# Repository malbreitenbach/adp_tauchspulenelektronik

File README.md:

# adp_tauchspulenelektronik
ADP Tauchspulenelektronik (Versions-/Projektmanagement)

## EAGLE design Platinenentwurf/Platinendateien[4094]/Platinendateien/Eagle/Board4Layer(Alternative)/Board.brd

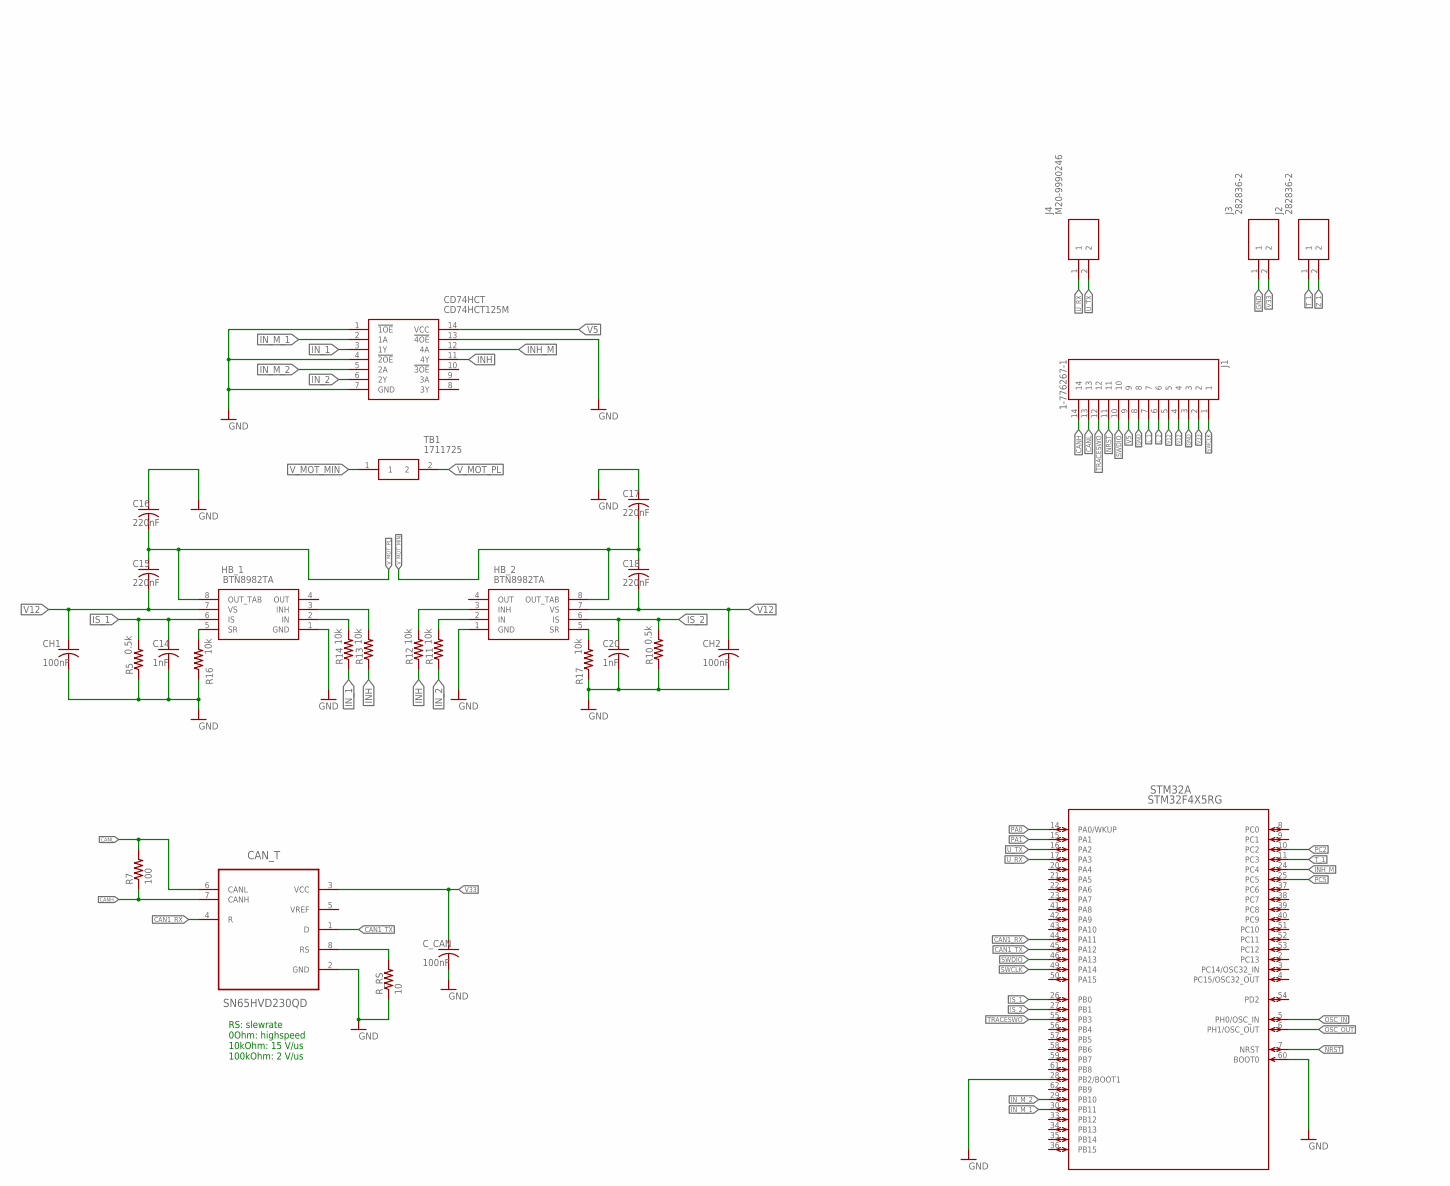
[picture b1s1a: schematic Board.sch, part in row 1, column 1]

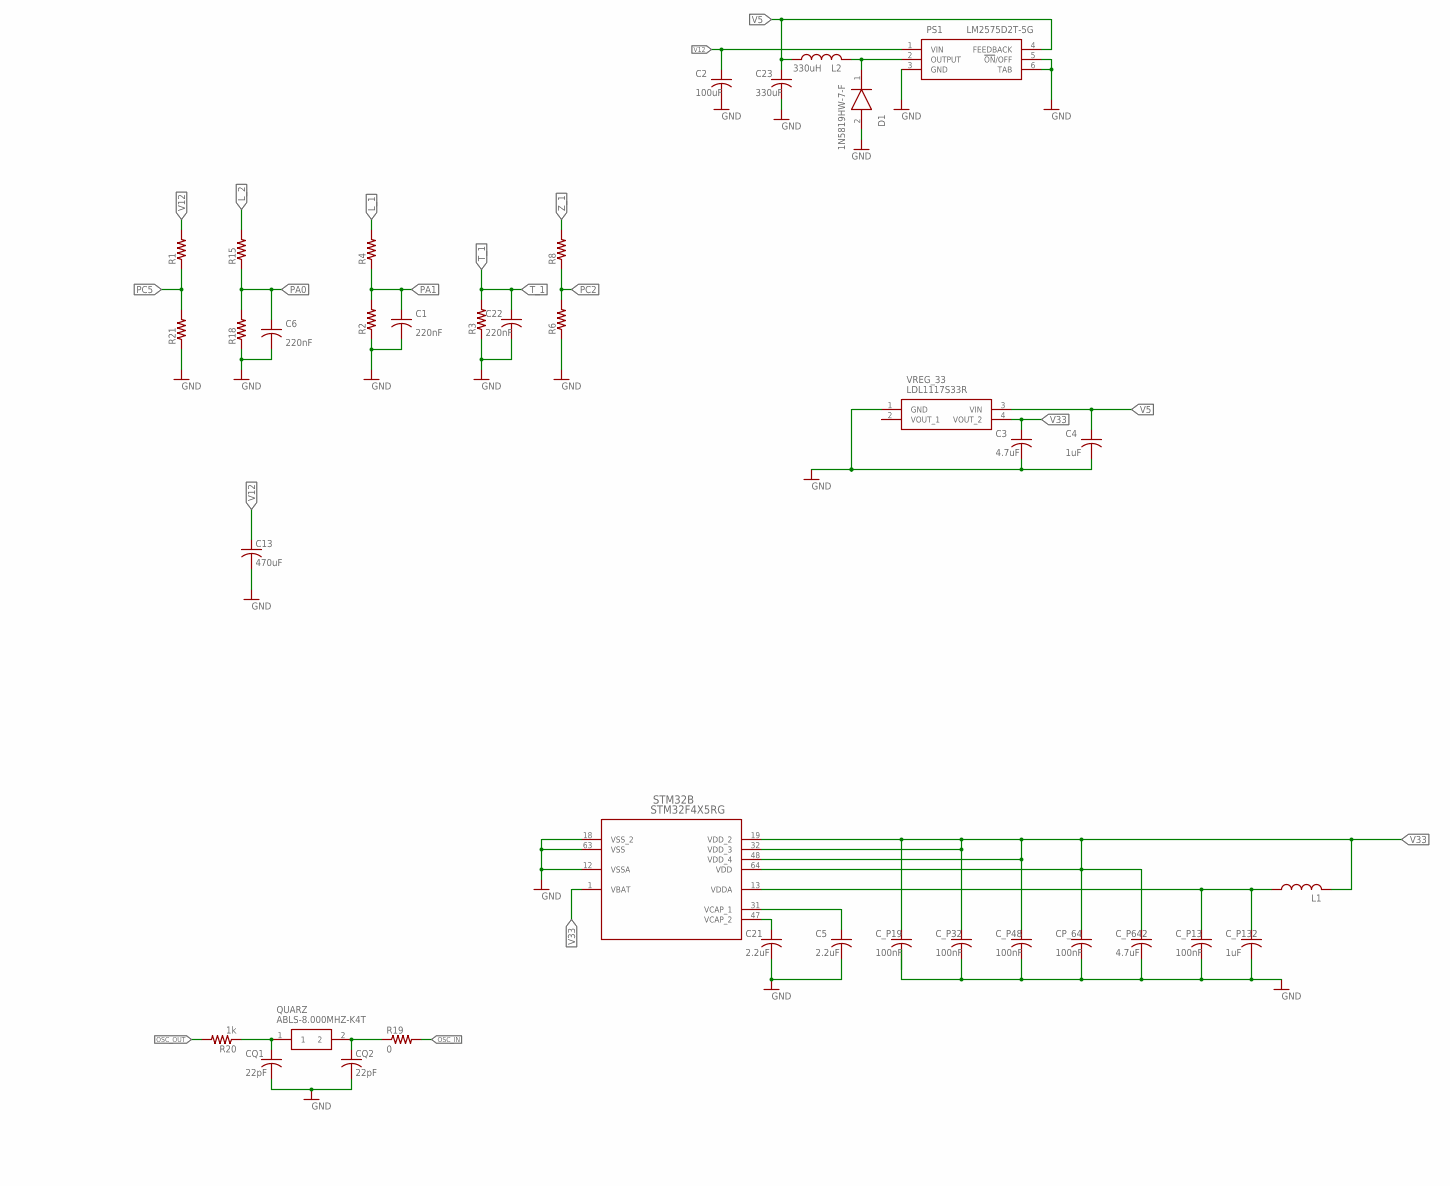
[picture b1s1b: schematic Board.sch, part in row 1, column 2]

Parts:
C1, C6, C15, C16, C17, C18, C22: 220nF; C0805
C2: 100uF; C0805
C3: 4.7uF; C0805
C4: 1uF; C0805
C5, C21: 2.2uF; C0805
C13: 470uF; C050-075X075
C14, C20: 1nF; C0805
C23: 330uF; C0805
CAN_T: SN65HVD230QD; SOIC127P600X175-8N; MPN SN65HVD230QD..
CD74HCT: CD74HCT125M; SOIC127P600X175-14N
CH1, CH2: 100nF; C0805
CP_64: 100nF; C0805
CQ1, CQ2: 22pF; C0805
C_CAN: 100nF; C0805
C_P13, C_P19, C_P32, C_P48: 100nF; C0805
C_P132: 1uF; C0805
C_P642: 4.7uF; C0805
D1: 1N5819HW-7-F; SOD3716X145N
HB_1, HB_2: BTN8982TA; TO127P1500X440-8N
J1: 1-776267-1; TE_1-776267-1
J2, J3: 282836-2; SHDR2W100P0X500_1X2_1000X820X1
J4: M20-9990246; HDRV2W64P0X254_1X2_508X254X864
L1: INDUCTOR_0805_N; RESC0805_N
L2: 330uH; RESC0805_N
PS1: LM2575D2T-5G; D2TSUFFIX-CASE936A-02-ISSUEC
QUARZ: ABLS-8.000MHZ-K4T; ABLS-12.000MHZ-B2; MPN ABLS-8.000MHZ-K4T
R1, R2, R3, R4, R6, R8, R15, R18, R21: R-US_R0805; R0805
R5, R10: 0.5k; R0805
R7: 100; R0805
R11, R12, R13, R14, R16, R17: 10k; R0805
R19: 0; R0805
R20: 1k; R0805
R_RS: 10; R0805
STM32: STM32F4X5RG; LQFP64-10X10MM
TB1: 1711725; PHEONIX-5.08PITCH-2PIN
VREG_33: LDL1117S33R; SOT230P700X180-4N; MPN LDL1117S33R

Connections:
CAN1_RX: CAN_T.4 (R), STM32.44 (PA11)
CAN1_TX: CAN_T.1 (D), STM32.45 (PA12)
CANH: CAN_T.7 (CANH), J1.14, R7.1
CANL: CAN_T.6 (CANL), J1.13, R7.2
CAN_RS: CAN_T.8 (RS), R_RS.2
GND: C1.2, C2.2, C3.2, C4.2, C5.2, C6.2, C13.2, C14.2, C16.1, C17.1, C20.2, C21.2, C22.2, C23.2, CAN_T.2 (GND), CD74HCT.1 (!1OE), CD74HCT.4 (!2OE), CD74HCT.7 (GND), CD74HCT.13 (!4OE), CH1.2, CH2.2, CP_64.2, CQ1.2, CQ2.2, C_CAN.2, C_P13.2, C_P19.2, C_P32.2, C_P48.2, C_P132.2, C_P642.2, D1.2 (A), HB_1.1 (GND), HB_2.1 (GND), J1.3, J1.8, J3.1, PS1.3 (GND), PS1.5 (!ON!/OFF), PS1.6 (TAB), R2.1, R3.1, R5.1, R6.1, R10.1, R16.1, R17.1, R18.1, R21.1, R_RS.1, STM32.12 (VSSA), STM32.18 (VSS_2), STM32.28 (PB2/BOOT1), STM32.60 (BOOT0), STM32.63 (VSS), VREG_33.1 (GND)
HB1_IN: HB_1.2 (IN), R14.2
HB1_INH: HB_1.3 (INH), R13.2
HB2_IN: HB_2.2 (IN), R11.2
HB2_INH: HB_2.3 (INH), R12.2
INH: CD74HCT.11 (4Y), R12.1, R13.1
INH_M: CD74HCT.12 (4A), STM32.24 (PC4)
IN_1: CD74HCT.3 (1Y), R14.1
IN_2: CD74HCT.6 (2Y), R11.1
IN_M_1: CD74HCT.2 (1A), STM32.30 (PB11)
IN_M_2: CD74HCT.5 (2A), STM32.29 (PB10)
IS_1: C14.1, HB_1.6 (IS), R5.2, STM32.26 (PB0)
IS_2: C20.1, HB_2.6 (IS), R10.2, STM32.27 (PB1)
L_1: J1.7, R4.2
L_2: J1.6, R15.2
unnamed: D1.1 (K), L2.2, PS1.2 (OUTPUT)
NRST: J1.11, STM32.7 (NRST)
OSC_IN: R19.2, STM32.5 (PH0/OSC_IN)
OSC_OUT: R20.2, STM32.6 (PH1/OSC_OUT)
PA0: C6.1, R15.1, R18.2, STM32.14 (PA0/WKUP)
PA1: C1.1, R2.2, R4.1, STM32.15 (PA1)
PC2: R6.2, R8.1, STM32.10 (PC2)
PC5: R1.1, R21.2, STM32.25 (PC5)
Q_IN: CQ2.1, QUARZ.2, R19.1
Q_OUT: CQ1.1, QUARZ.1, R20.1
SR1: HB_1.5 (SR), R16.2
SR2: HB_2.5 (SR), R17.2
SWCLK: J1.1, STM32.49 (PA14)
SWDIO: J1.10, STM32.46 (PA13)
TRACESWO: J1.12, STM32.55 (PB3)
T_1: C22.1, J2.1, R3.2, STM32.11 (PC3)
U_RX: J4.1, STM32.17 (PA3)
U_TX: J4.2, STM32.16 (PA2)
V5: C4.1, C23.1, CD74HCT.14 (VCC), J1.9, L2.1, PS1.4 (FEEDBACK), VREG_33.3 (VIN)
V12: C2.1, C13.1, C15.2, C18.2, CH1.1, CH2.1, HB_1.7 (VS), HB_2.7 (VS), J1.4, J1.5, PS1.1 (VIN), R1.2
V33: C3.1, CAN_T.3 (VCC), CP_64.1, C_CAN.1, C_P19.1, C_P32.1, C_P48.1, C_P642.1, J1.2, J3.2, L1.2, STM32.1 (VBAT), STM32.19 (VDD_2), STM32.32 (VDD_3), STM32.48 (VDD_4), STM32.64 (VDD), VREG_33.4 (VOUT_2)
VCAP_1: C5.1, STM32.31 (VCAP_1)
VCAP_2: C21.1, STM32.47 (VCAP_2)
VDDA: C_P13.1, C_P132.1, L1.1, STM32.13 (VDDA)
V_MOT_MIN: C17.2, C18.1, HB_2.8 (OUT_TAB), TB1.1
V_MOT_PL: C15.1, C16.2, HB_1.8 (OUT_TAB), TB1.2
Z_1: J2.2, R8.2

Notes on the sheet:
RS: slewrate 0Ohm: highspeed 10kOhm: 15 V/us 100kOhm: 2 V/us

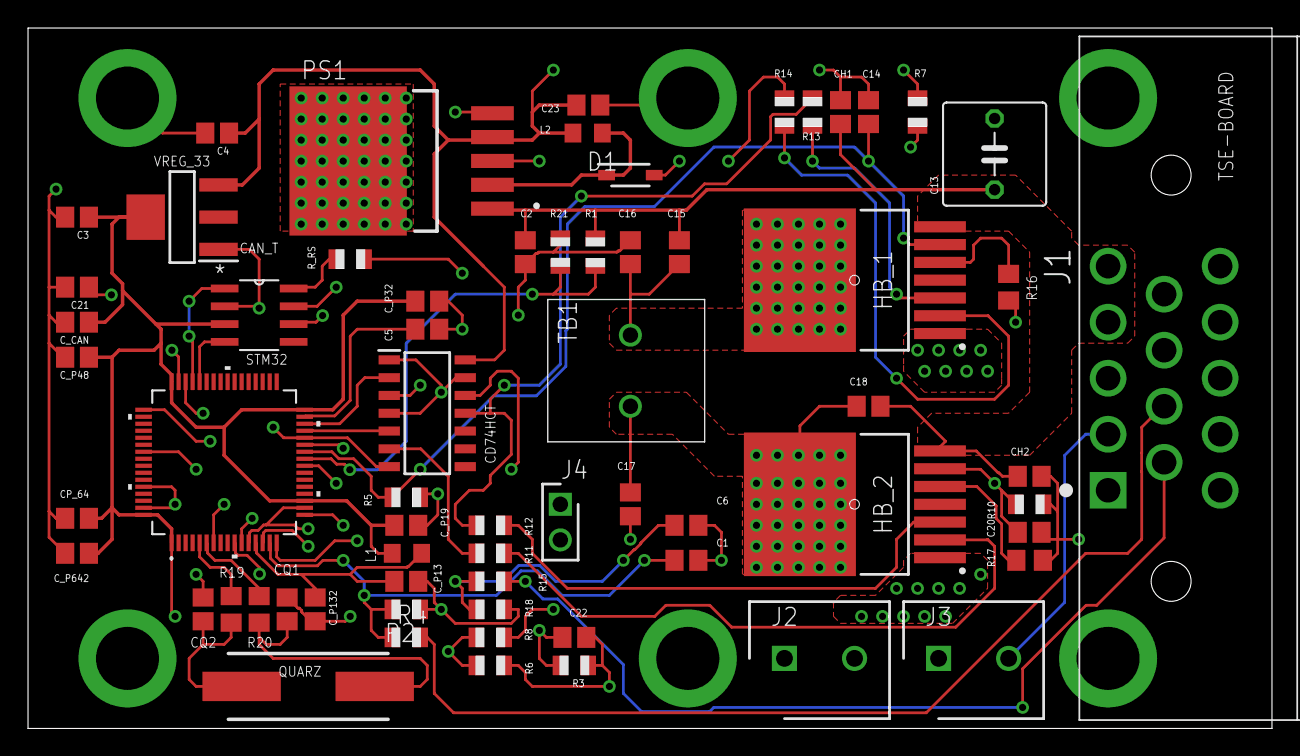
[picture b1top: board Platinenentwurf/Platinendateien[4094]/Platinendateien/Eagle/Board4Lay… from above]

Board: 4 copper layers, 88.8 x 50.0 mm, 65 parts (0 on the bottom side), 47 nets.

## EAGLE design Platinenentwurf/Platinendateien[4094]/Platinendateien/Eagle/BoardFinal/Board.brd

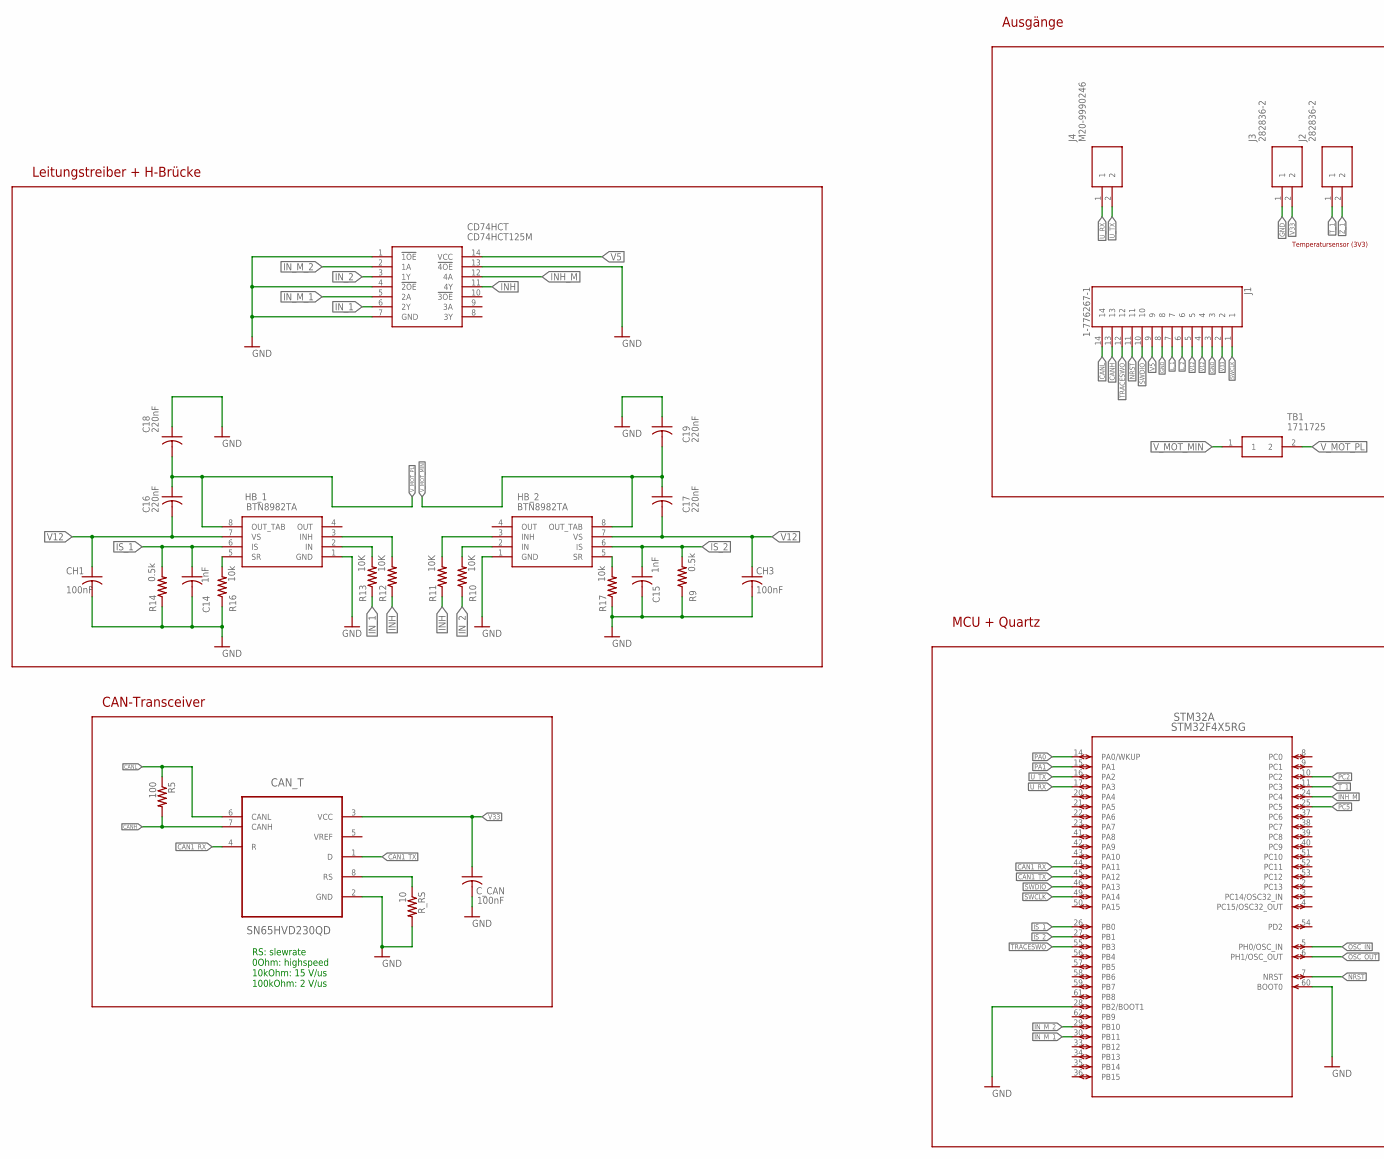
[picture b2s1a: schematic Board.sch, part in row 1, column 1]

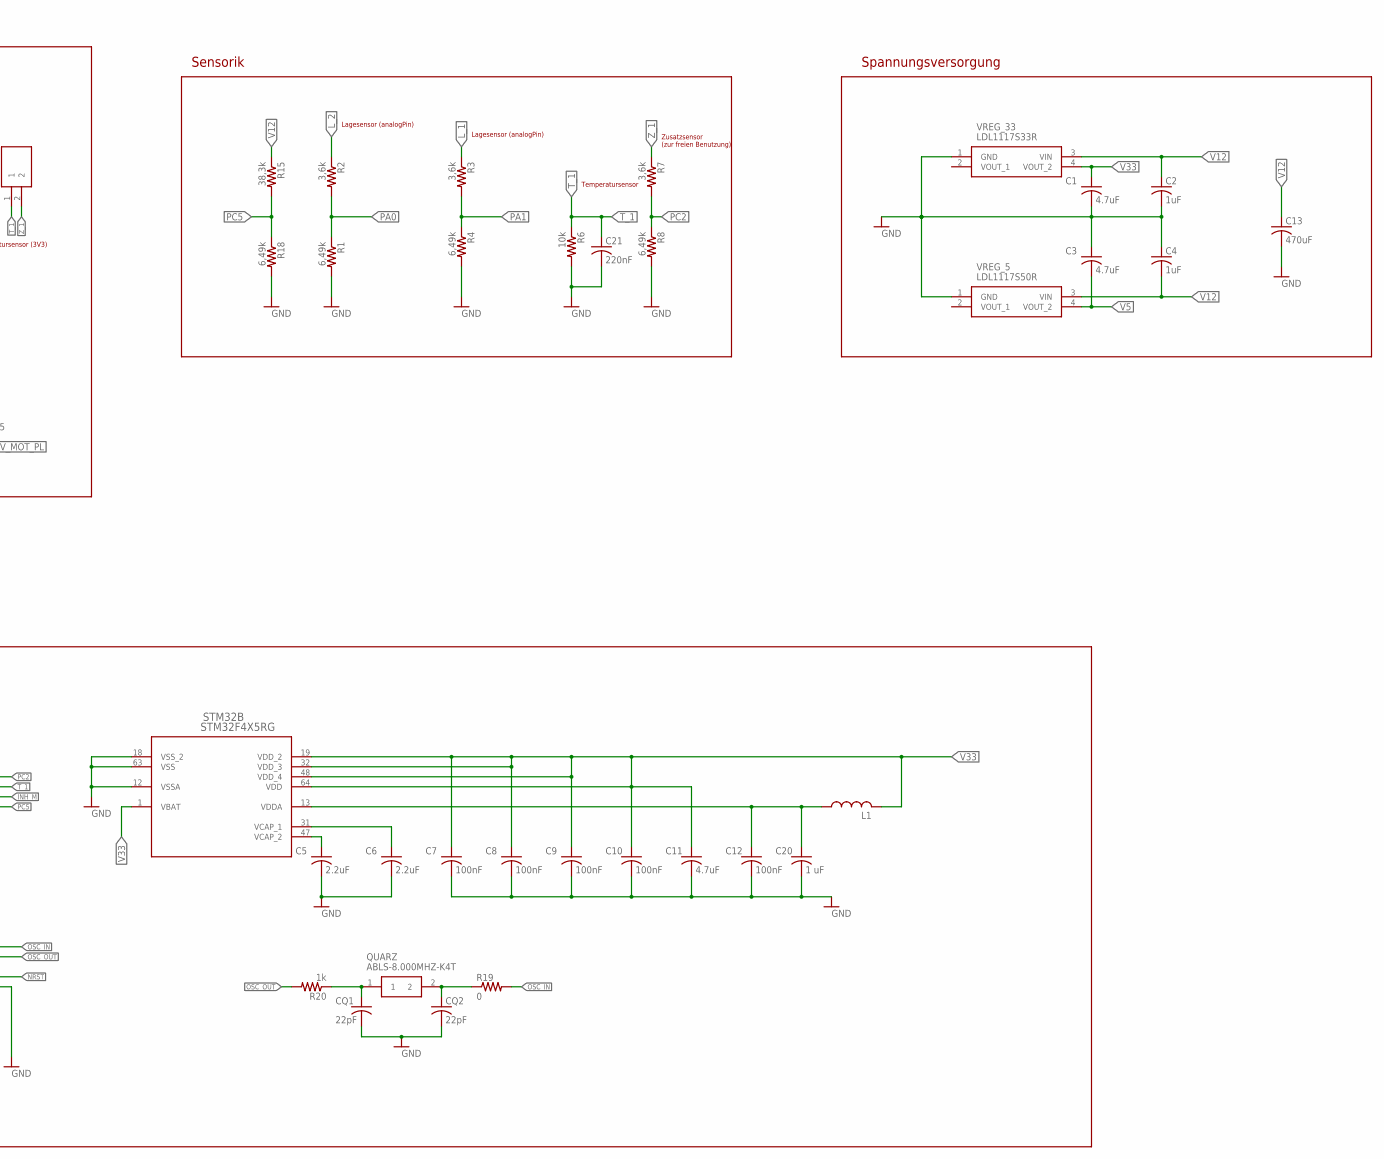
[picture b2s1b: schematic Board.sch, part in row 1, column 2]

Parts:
C1, C3, C11: 4.7uF; C1206
C2, C4: 1uF; C1206
C5, C6: 2.2uF; C1206
C7, C8, C9, C10, C12: 100nF; C1206
C13: 470uF; C050-075X075
C14, C15: 1nF; C1206
C16, C17, C18, C19, C21: 220nF; C1206
C20: 1 uF; C1206
CAN_T: SN65HVD230QD; SOIC127P600X175-8N; MPN SN65HVD230QD..
CD74HCT: CD74HCT125M; SOIC127P600X175-14N
CH1, CH3: 100nF; C1206
CQ1, CQ2: 22pF; C0805
C_CAN: 100nF; C1206
HB_1, HB_2: BTN8982TA; TO127P1500X440-8N
J1: 1-776267-1; TE_1-776267-1
J2, J3: 282836-2; SHDR2W100P0X500_1X2_1000X820X1
J4: M20-9990246; HDRV2W64P0X254_1X2_508X254X864
L1: INDUCTOR_0805_N; RESC0805_N
QUARZ: ABLS-8.000MHZ-K4T; ABLS-12.000MHZ-B2; MPN ABLS-8.000MHZ-K4T
R1, R4, R8, R18: 6,49k; R1206
R2, R3, R7: 3,6k; R1206
R5: 100; R1206
R6: 10k; R1206
R9, R14: 0.5k; R1206
R10, R11, R12, R13: 10K; R1206
R15: 38,3k; R1206
R16, R17: 10k; R0805
R19: 0; R0805
R20: 1k; R0805
R_RS: 10; R1206
STM32: STM32F4X5RG; LQFP64-10X10MM
TB1: 1711725; PHEONIX-5.08PITCH-2PIN
VREG_5: LDL1117S50R; SOT230P700X180-4N; MPN LDL1117S50R
VREG_33: LDL1117S33R; SOT230P700X180-4N; MPN LDL1117S33R

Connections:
CAN1_RX: CAN_T.4 (R), STM32.44 (PA11)
CAN1_TX: CAN_T.1 (D), STM32.45 (PA12)
CANH: CAN_T.7 (CANH), J1.13, R5.2
CANL: CAN_T.6 (CANL), J1.14, R5.1
CAN_RS: CAN_T.8 (RS), R_RS.1
GND: C1.2, C2.2, C3.1, C4.1, C5.2, C6.2, C7.2, C8.2, C9.2, C10.2, C11.2, C12.2, C13.2, C14.2, C15.2, C18.1, C19.1, C20.2, C21.2, CAN_T.2 (GND), CD74HCT.1 (!1OE), CD74HCT.4 (!2OE), CD74HCT.7 (GND), CD74HCT.13 (!4OE), CH1.2, CH3.2, CQ1.2, CQ2.2, C_CAN.2, HB_1.1 (GND), HB_2.1 (GND), J1.3, J1.8, J3.1, R1.2, R4.2, R6.2, R8.2, R9.1, R14.1, R16.1, R17.1, R18.2, R_RS.2, STM32.12 (VSSA), STM32.18 (VSS_2), STM32.28 (PB2/BOOT1), STM32.60 (BOOT0), STM32.63 (VSS), VREG_5.1 (GND), VREG_33.1 (GND)
HB1_IN: HB_1.2 (IN), R13.2
HB1_INH: HB_1.3 (INH), R12.2
HB2_IN: HB_2.2 (IN), R10.2
HB2_INH: HB_2.3 (INH), R11.2
INH: CD74HCT.11 (4Y), R11.1, R12.1
INH_M: CD74HCT.12 (4A), STM32.24 (PC4)
IN_1: CD74HCT.6 (2Y), R13.1
IN_2: CD74HCT.3 (1Y), R10.1
IN_M_1: CD74HCT.5 (2A), STM32.30 (PB11)
IN_M_2: CD74HCT.2 (1A), STM32.29 (PB10)
IS_1: C14.1, HB_1.6 (IS), R14.2, STM32.26 (PB0)
IS_2: C15.1, HB_2.6 (IS), R9.2, STM32.27 (PB1)
L_1: J1.7, R3.1
L_2: J1.6, R2.1
NRST: J1.11, STM32.7 (NRST)
OSC_IN: R19.2, STM32.5 (PH0/OSC_IN)
OSC_OUT: R20.2, STM32.6 (PH1/OSC_OUT)
PA0: R1.1, R2.2, STM32.14 (PA0/WKUP)
PA1: R3.2, R4.1, STM32.15 (PA1)
PC2: R7.2, R8.1, STM32.10 (PC2)
PC5: R15.2, R18.1, STM32.25 (PC5)
Q_IN: CQ2.1, QUARZ.2, R19.1
Q_OUT: CQ1.1, QUARZ.1, R20.1
SR1: HB_1.5 (SR), R16.2
SR2: HB_2.5 (SR), R17.2
SWCLK: J1.1, STM32.49 (PA14)
SWDIO: J1.10, STM32.46 (PA13)
TRACESWO: J1.12, STM32.55 (PB3)
T_1: C21.1, J2.1, R6.1, STM32.11 (PC3)
U_RX: J4.1, STM32.17 (PA3)
U_TX: J4.2, STM32.16 (PA2)
V5: C3.2, CD74HCT.14 (VCC), J1.9, VREG_5.4 (VOUT_2)
V12: C2.1, C4.2, C13.1, C16.2, C17.2, CH1.1, CH3.1, HB_1.7 (VS), HB_2.7 (VS), J1.4, J1.5, R15.1, VREG_5.3 (VIN), VREG_33.3 (VIN)
V33: C1.1, C7.1, C8.1, C9.1, C10.1, C11.1, CAN_T.3 (VCC), C_CAN.1, J1.2, J3.2, L1.2, STM32.1 (VBAT), STM32.19 (VDD_2), STM32.32 (VDD_3), STM32.48 (VDD_4), STM32.64 (VDD), VREG_33.4 (VOUT_2)
VCAP_1: C6.1, STM32.31 (VCAP_1)
VCAP_2: C5.1, STM32.47 (VCAP_2)
VDDA: C12.1, C20.1, L1.1, STM32.13 (VDDA)
V_MOT_MIN: C17.1, C19.2, HB_2.8 (OUT_TAB), TB1.1
V_MOT_PL: C16.1, C18.2, HB_1.8 (OUT_TAB), TB1.2
Z_1: J2.2, R7.1

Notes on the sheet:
RS: slewrate 0Ohm: highspeed 10kOhm: 15 V/us 100kOhm: 2 V/us
Sensorik
Spannungsversorgung
MCU + Quartz
Ausgänge
CAN-Transceiver
Leitungstreiber + H-Brücke
Lagesensor (analogPin)
Zusatzsensor (zur freien Benutzung)
Temperatursensor
Temperatursensor (3V3)

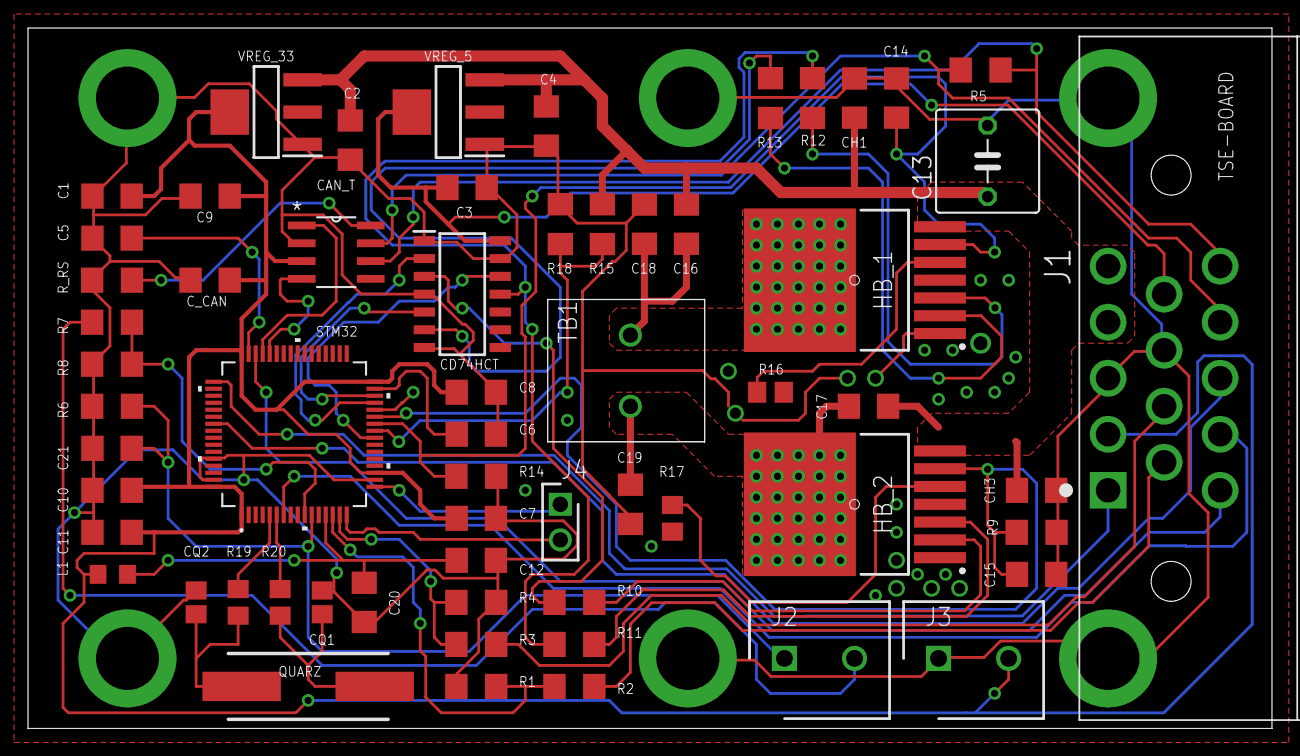
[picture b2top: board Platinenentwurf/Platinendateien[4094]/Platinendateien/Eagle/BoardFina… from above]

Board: 2 copper layers, 88.8 x 50.0 mm, 61 parts (0 on the bottom side), 46 nets.

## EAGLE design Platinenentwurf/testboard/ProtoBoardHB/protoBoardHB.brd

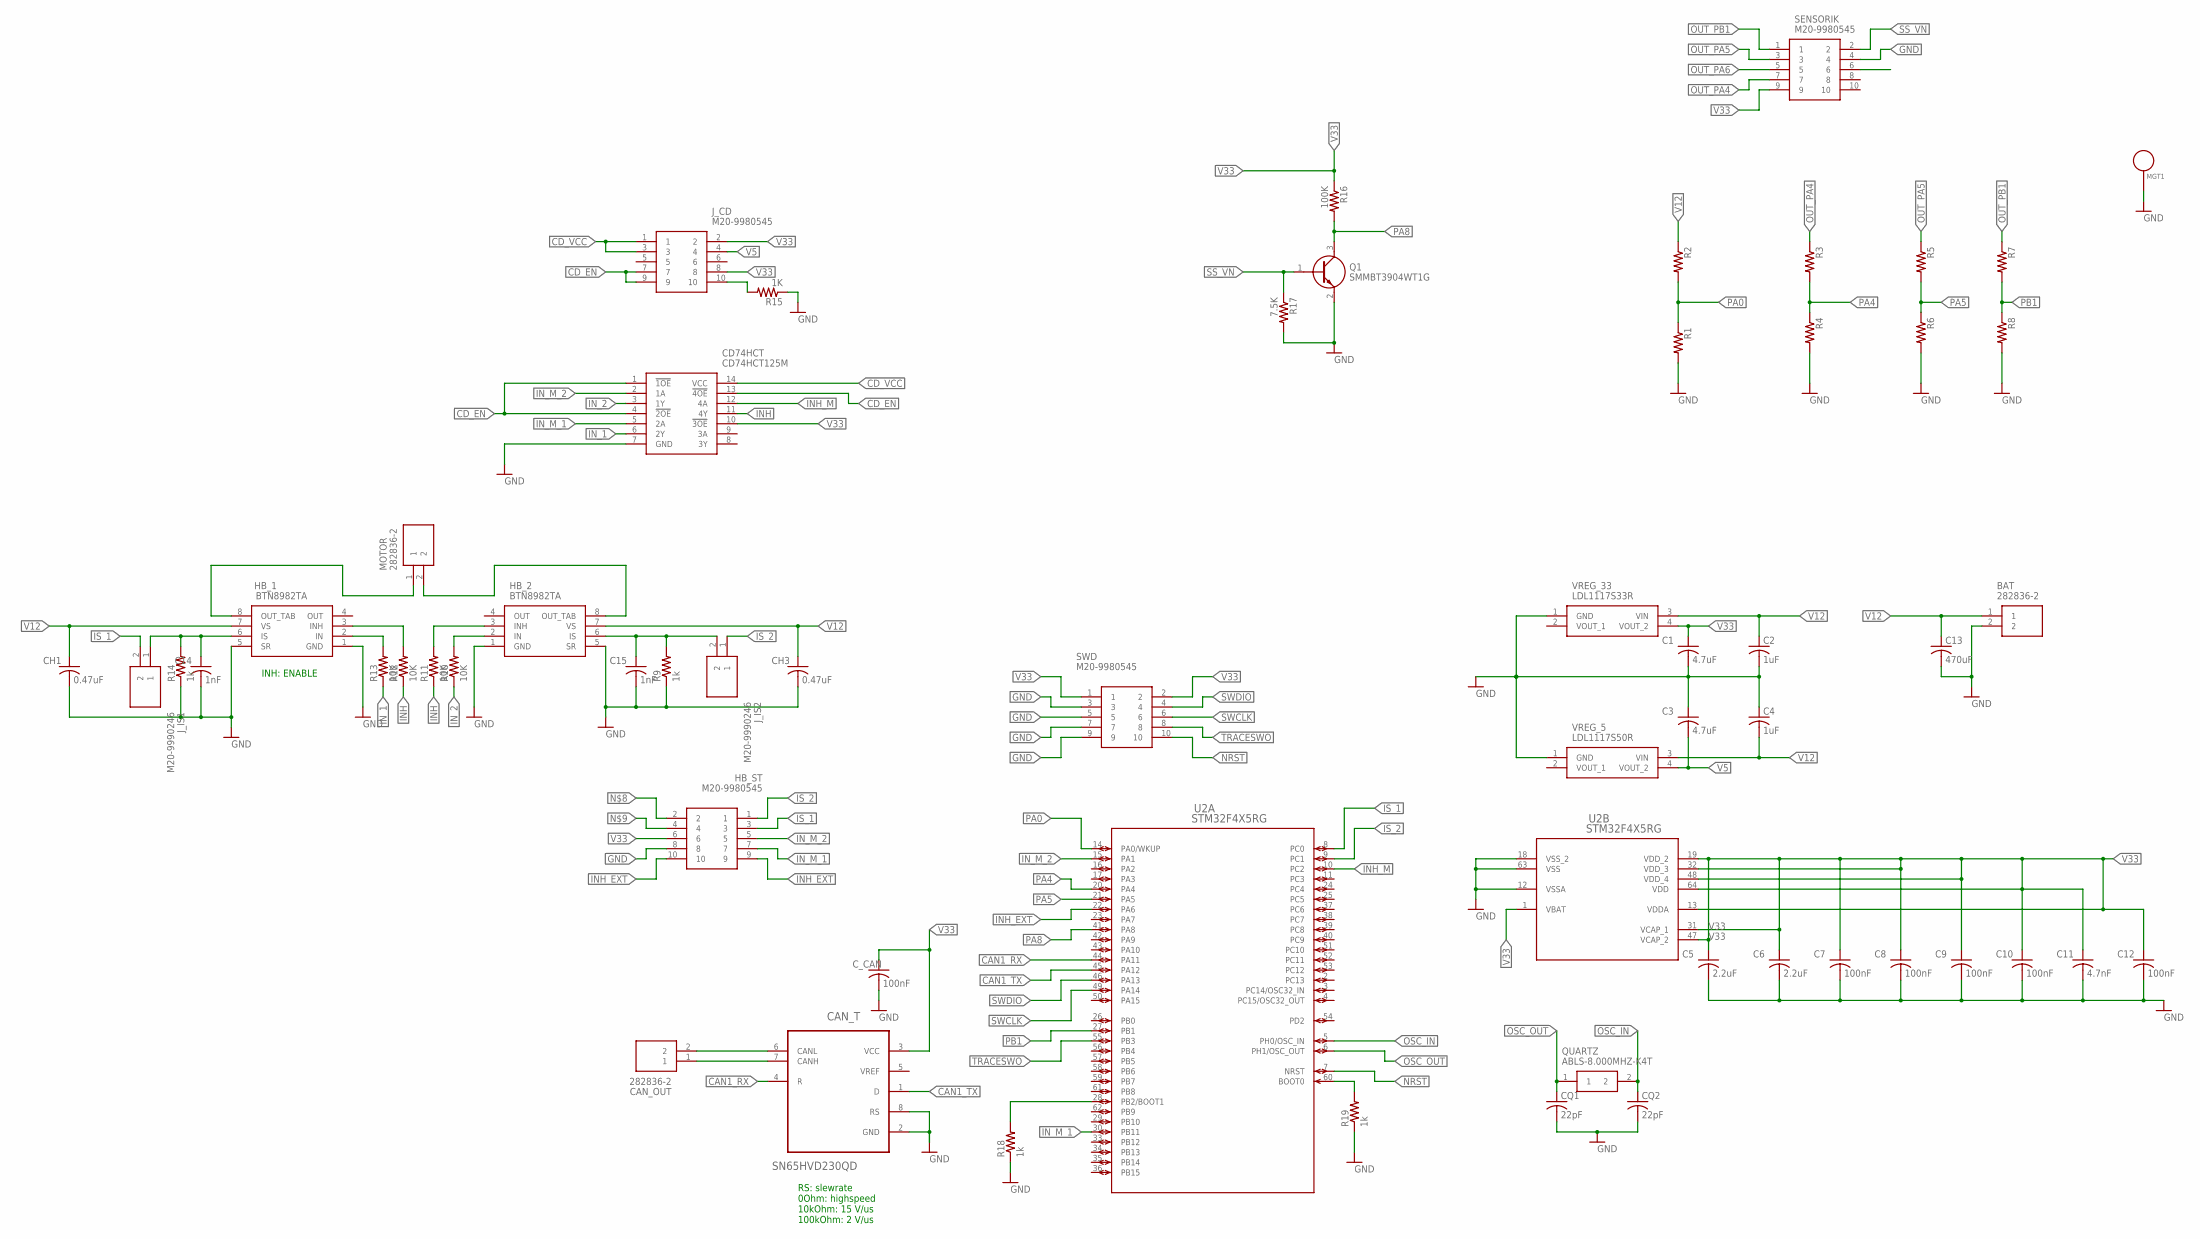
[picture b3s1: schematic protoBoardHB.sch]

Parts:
BAT: 282836-2; SHDR2W100P0X500_1X2_1000X820X1
C1, C3: 4.7uF; C1206
C2, C4: 1uF; C1206
C5, C6: 2.2uF; C1206
C7, C8, C9, C10, C12: 100nF; C1206
C11: 4.7nF; C1206
C13: 470uF; C050-075X075
C14, C15: 1nF; C1206
CAN_OUT: 282836-2; SHDR2W100P0X500_1X2_1000X820X1
CAN_T: SN65HVD230QD; SOIC127P600X175-8N; MPN SN65HVD230QD..
CD74HCT: CD74HCT125M; SOIC127P600X175-14N
CH1, CH3: 0.47uF; C1206
CQ1, CQ2: 22pF; C0805
C_CAN: 100nF; C1206
HB_1, HB_2: BTN8982TA; TO127P1500X440-8N
HB_ST: M20-9980545; HDRV10W80P254_2X5_1270X508X864; MPN M20-9980545
J_CD: M20-9980545; HDRV10W80P254_2X5_1270X508X864
J_IS1, J_IS2: M20-9990246; HDRV2W64P0X254_1X2_508X254X864
MGT1: BEAGLEBONEBLACK_MOUNTING_HOLE
MOTOR: 282836-2; SHDR2W100P0X500_1X2_1000X820X1
Q1: SMMBT3904WT1G; SOT65P220X100-3N
QUARTZ: ABLS-8.000MHZ-K4T; ABLS-12.000MHZ-B2; MPN ABLS-8.000MHZ-K4T
R1, R2, R3, R4, R5, R6, R7, R8: R-US_R1206; R1206
R9, R14, R18, R19: 1k; R1206
R10, R11, R12, R13: 10K; R1206
R15: 1K; R1206
R16: 100K; R1206
R17: 7.5K; R1206
SENSORIK: M20-9980545; HDRV10W80P254_2X5_1270X508X864
SWD: M20-9980545; HDRV10W80P254_2X5_1270X508X864; MPN M20-9980545
U2: STM32F4X5RG; LQFP64-10X10MM
VREG_5: LDL1117S50R; SOT230P700X180-4N; MPN LDL1117S50R
VREG_33: LDL1117S33R; SOT230P700X180-4N; MPN LDL1117S33R

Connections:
BOOT0: R19.2, U2.60 (BOOT0)
BOOT1: R18.2, U2.28 (PB2/BOOT1)
CAN1_RX: CAN_T.4 (R), U2.44 (PA11)
CAN1_TX: CAN_T.1 (D), U2.45 (PA12)
CANH: CAN_OUT.1, CAN_T.7 (CANH)
CANL: CAN_OUT.2, CAN_T.6 (CANL)
CD_EN: CD74HCT.1 (!1OE), CD74HCT.4 (!2OE), CD74HCT.13 (!4OE), J_CD.7, J_CD.9
CD_VCC: CD74HCT.14 (VCC), J_CD.1, J_CD.3
GND: BAT.2, C1.2, C2.2, C3.1, C4.1, C5.2, C6.2, C7.2, C8.2, C9.2, C10.2, C11.2, C12.2, C13.2, C14.2, C15.2, CAN_T.2 (GND), CAN_T.8 (RS), CD74HCT.7 (GND), CH1.2, CH3.2, CQ1.2, CQ2.2, C_CAN.2, HB_1.1 (GND), HB_1.5 (SR), HB_2.1 (GND), HB_2.5 (SR), HB_ST.8, MGT1.P$1, Q1.2 (E), R1.2, R4.2, R6.2, R8.2, R9.1, R14.1, R15.1, R17.2, R18.1, R19.1, SENSORIK.4, SWD.3, SWD.5, SWD.7, SWD.9, U2.12 (VSSA), U2.18 (VSS_2), U2.63 (VSS), VREG_5.1 (GND), VREG_33.1 (GND)
INH: CD74HCT.11 (4Y), R11.1, R12.1
INH_EXT: HB_ST.9, HB_ST.10, U2.22 (PA6)
INH_M: CD74HCT.12 (4A), U2.10 (PC2)
IN_1: CD74HCT.6 (2Y), R13.1
IN_2: CD74HCT.3 (1Y), R10.1
IN_M_1: CD74HCT.5 (2A), HB_ST.7, U2.30 (PB11)
IN_M_2: CD74HCT.2 (1A), HB_ST.5, U2.15 (PA1)
IS_1: HB_ST.3, J_IS1.2, U2.8 (PC0)
IS_2: HB_ST.1, J_IS2.1, U2.9 (PC1)
unnamed: J_CD.10, R15.2
unnamed: C15.1, HB_2.6 (IS), J_IS2.2, R9.2
unnamed: HB_1.2 (IN), R13.2
unnamed: HB_1.3 (INH), R12.2
unnamed: HB_2.2 (IN), R10.2
unnamed: HB_2.3 (INH), R11.2
unnamed: C14.1, HB_1.6 (IS), J_IS1.1, R14.2
NRST: SWD.10, U2.7 (NRST)
OSC_IN: CQ2.1, QUARTZ.2, U2.5 (PH0/OSC_IN)
OSC_OUT: CQ1.1, QUARTZ.1, U2.6 (PH1/OSC_OUT)
OUT_PA4: R3.1, SENSORIK.7
OUT_PA5: R5.1, SENSORIK.3
OUT_PA6: SENSORIK.5
OUT_PB1: R7.1, SENSORIK.1
PA0: R1.1, R2.2, U2.14 (PA0/WKUP)
PA4: R3.2, R4.1, U2.20 (PA4)
PA5: R5.2, R6.1, U2.21 (PA5)
PA8: Q1.3 (C), R16.2, U2.41 (PA8)
PB1: R7.2, R8.1, U2.27 (PB1)
SS_VN: Q1.1 (B), R17.1, SENSORIK.2
SWCLK: SWD.6, U2.49 (PA14)
SWDIO: SWD.4, U2.46 (PA13)
TRACESWO: SWD.8, U2.55 (PB3)
V5: C3.2, J_CD.4, VREG_5.4 (VOUT_2)
V12: BAT.1, C2.1, C4.2, C13.1, CH1.1, CH3.1, HB_1.7 (VS), HB_2.7 (VS), R2.1, VREG_5.3 (VIN), VREG_33.3 (VIN)
V33: C1.1, C5.1, C6.1, C7.1, C8.1, C9.1, C10.1, C11.1, C12.1, CAN_T.3 (VCC), CD74HCT.10 (!3OE), C_CAN.1, HB_ST.6, J_CD.2, J_CD.8, R16.1, SENSORIK.9, SWD.1, SWD.2, U2.1 (VBAT), U2.13 (VDDA), U2.19 (VDD_2), U2.31 (VCAP_1), U2.32 (VDD_3), U2.47 (VCAP_2), U2.48 (VDD_4), U2.64 (VDD), VREG_33.4 (VOUT_2)
V_MOT_MIN: HB_2.8 (OUT_TAB), MOTOR.2
V_MOT_PL: HB_1.8 (OUT_TAB), MOTOR.1

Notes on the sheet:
RS: slewrate 0Ohm: highspeed 10kOhm: 15 V/us 100kOhm: 2 V/us
INH: ENABLE

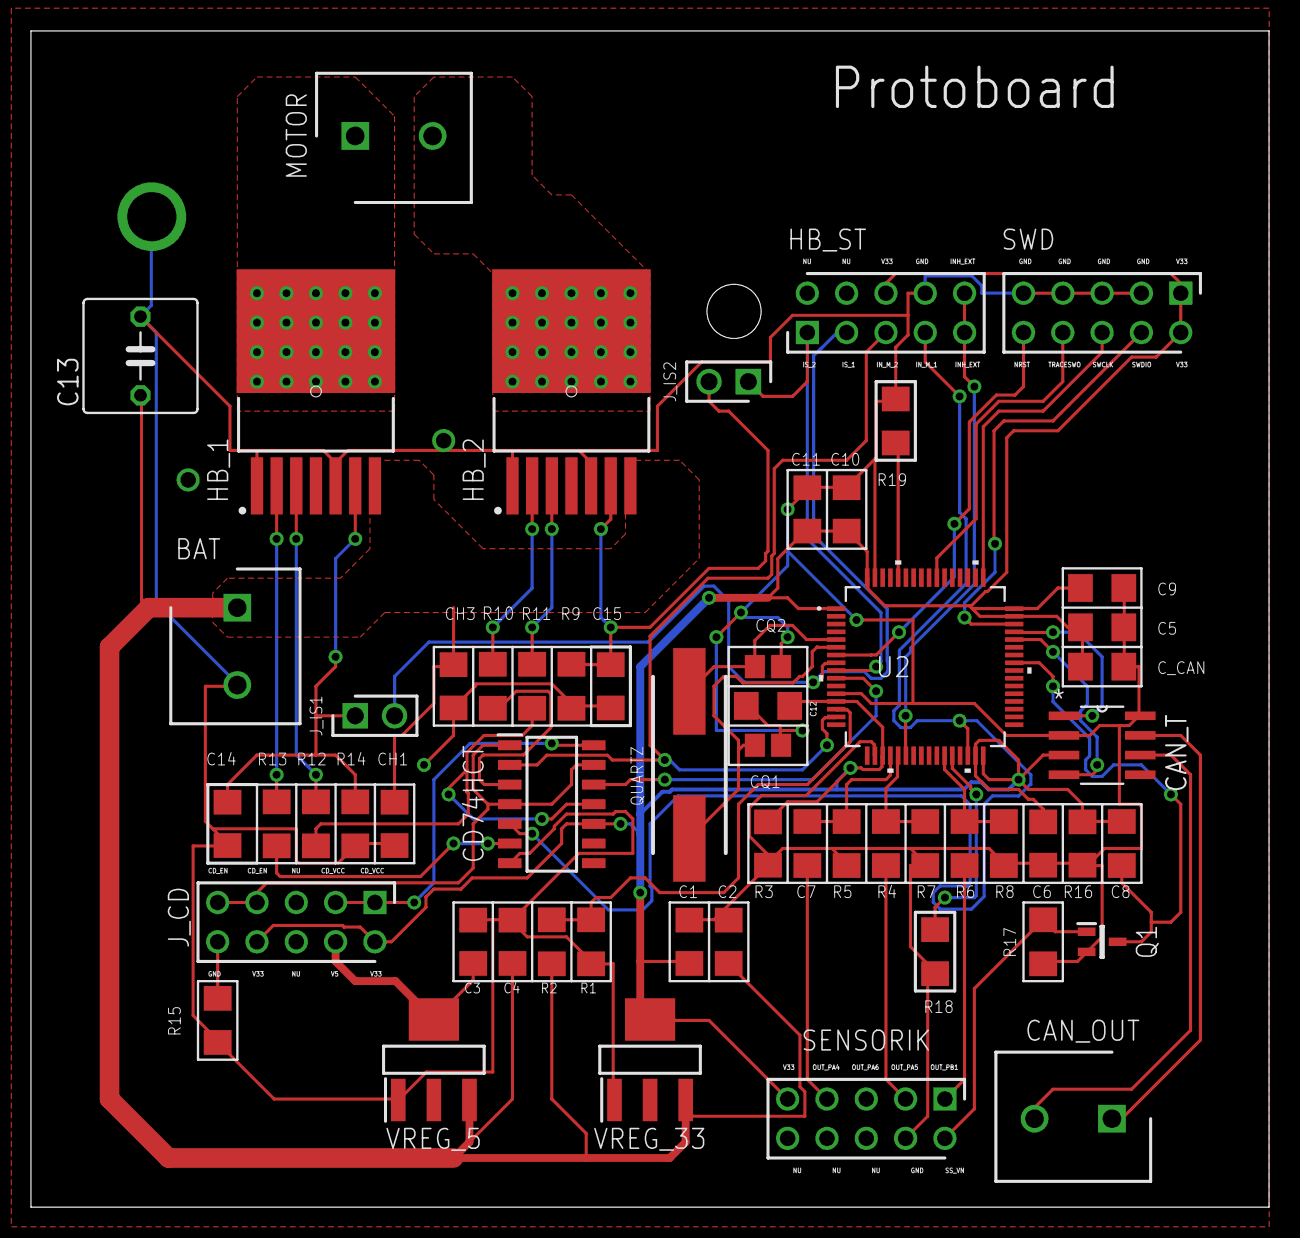
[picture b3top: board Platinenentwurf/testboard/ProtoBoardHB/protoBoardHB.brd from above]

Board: 2 copper layers, 80.0 x 76.0 mm, 58 parts (0 on the bottom side), 45 nets.

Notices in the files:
parts and their libraries:
SparkFun-PowerSymbols: Licensing: Creative Commons ShareAlike 4.0 International - https://creativecommons.org/licenses/by-sa/4.0
